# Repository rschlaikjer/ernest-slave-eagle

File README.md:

# Ernest Slave Node Schematics
Eagle files for data collection nodes

[Master Project Repo](https://github.com/rschlaikjer/Ernest)

## What is this
Ernest is the next step of the [ArNest](https://github.com/rschlaikjer/ArNest),
and takes it from a single-location thermostat to a many node system consisting
of a base station and one or more smaller nodes that collect and report
atmospheric data to the base. This way the system can monitor multiple rooms, as
well as the outside conditions.

These EAGLE files show the schematic for hooking up the slave nodes, as well as
a board layout for printing your own slave boards.

For the code to run on the slave nodes,
[see here](https://github.com/rschlaikjer/ernest-slave-code).

## Parts list
(All prices per unit and approximate)

- ($2.00) Atmega 328P (with arduino-style bootloader)
- ($3.19) USB FTDI programmer
- ($1.50) BMP180 breakout board
- ($13.75) (Optional) HIH-6130 humidity sensor
- ($0.98) nrf24L01 wireless transciever
- ($0.39) LM1117 3.3V regulator
- ($0.07) 16 MHz crystal oscillator
- ($0.03) 22pF capacitors
- ($0.08) Momentary reset switch
- ($0.32) 4-pin DIP switch
- ($0.01) 320 Ohm resistors
- ($0.03) LEDs
- ($0.30) 2.5mm barrel jack (for power)

**Total BOM: Approx. $5.86 per board** + 13.75 for humidity, as well as the cost
of PCB manufacture.

## Pretty Pictures

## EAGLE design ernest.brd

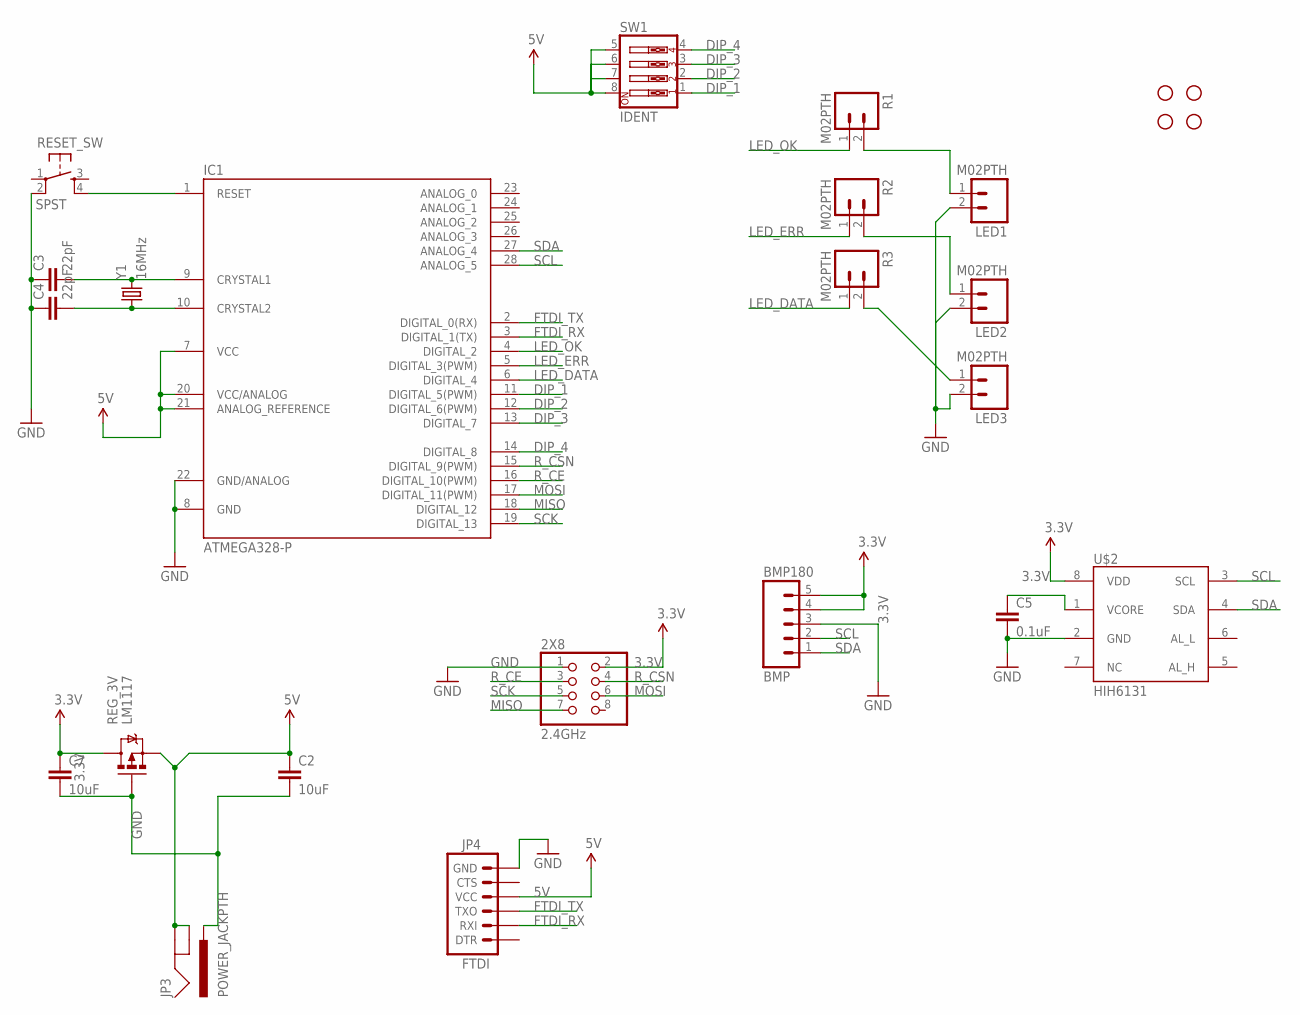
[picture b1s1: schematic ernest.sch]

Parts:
2X8: 2.4GHz; 2X04
BMP180: BMP; 1X05
C2, C7: 10uF; CAP-PTH-SMALL
C3, C4: 22pF; CAP-PTH-SMALL
C5: 0.1uF; CAP-PTH-SMALL
IC1: ATMEGA328-P; DIL28-3
JP3: POWER_JACKPTH; POWER_JACK_PTH
JP4: FTDI; 1X06
LED1, LED2, LED3: M02PTH; 1X02
R1, R2, R3: M02PTH; 1X02
REG_3V: LM1117; TO220V
RESET_SW: SPST; TAC-SWITCH-PTH
STANDOFF1, STANDOFF2, STANDOFF3, STANDOFF4: STAND-OFF
SW1: IDENT; EDG-04
U$2: HIH6131; SOIC8
Y1: 16MHz; HC49US

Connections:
3.3V: 2X8.2, BMP180.4, BMP180.5, C7.1, REG_3V.2 (D), U$2.8 (VDD)
5V: C2.1, IC1.7 (VCC), IC1.20 (VCC/ANALOG), IC1.21 (ANALOG_REFERENCE), JP3.GND, JP3.GNDBREAK, JP4.4 (VCC), REG_3V.3 (S), SW1.5, SW1.6, SW1.7, SW1.8
DIP_1: IC1.11 (DIGITAL_5(PWM)), SW1.1
DIP_2: IC1.12 (DIGITAL_6(PWM)), SW1.2
DIP_3: IC1.13 (DIGITAL_7), SW1.3
DIP_4: IC1.14 (DIGITAL_8), SW1.4
FTDI_RX: IC1.3 (DIGITAL_1(TX)), JP4.2 (RXI)
FTDI_TX: IC1.2 (DIGITAL_0(RX)), JP4.3 (TXO)
GND: 2X8.1, BMP180.3, C2.2, C3.1, C4.1, C5.2, C7.2, IC1.8 (GND), IC1.22 (GND/ANALOG), JP3.PWR, JP4.6 (GND), LED1.2, LED2.2, LED3.2, REG_3V.1 (G), RESET_SW.2, U$2.2 (GND)
LED_DATA: IC1.6 (DIGITAL_4), R3.1
LED_ERR: IC1.5 (DIGITAL_3(PWM)), R2.1
LED_OK: IC1.4 (DIGITAL_2), R1.1
MISO: 2X8.7, IC1.18 (DIGITAL_12)
MOSI: 2X8.6, IC1.17 (DIGITAL_11(PWM))
unnamed: LED1.1, R1.2
unnamed: LED2.1, R2.2
unnamed: LED3.1, R3.2
unnamed: IC1.1 (RESET), RESET_SW.4
unnamed: C5.1, U$2.1 (VCORE)
unnamed: C3.2, IC1.9 (CRYSTAL1), Y1.2
unnamed: C4.2, IC1.10 (CRYSTAL2), Y1.1
R_CE: 2X8.3, IC1.16 (DIGITAL_10(PWM))
R_CSN: 2X8.4, IC1.15 (DIGITAL_9(PWM))
SCK: 2X8.5, IC1.19 (DIGITAL_13)
SCL: BMP180.2, IC1.28 (ANALOG_5), U$2.3 (SCL)
SDA: BMP180.1, IC1.27 (ANALOG_4), U$2.4 (SDA)

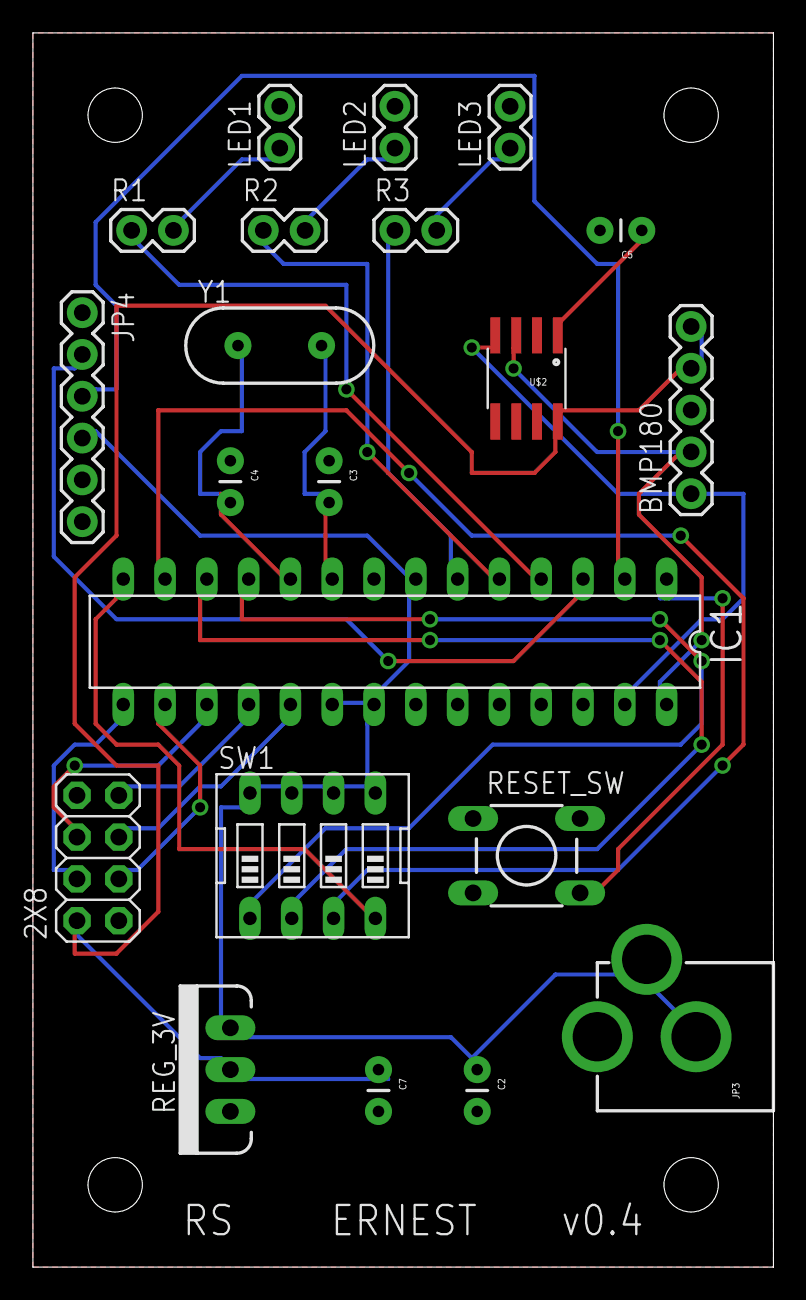
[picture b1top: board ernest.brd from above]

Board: 2 copper layers, 45.0 x 75.0 mm, 25 parts (0 on the bottom side), 26 nets.

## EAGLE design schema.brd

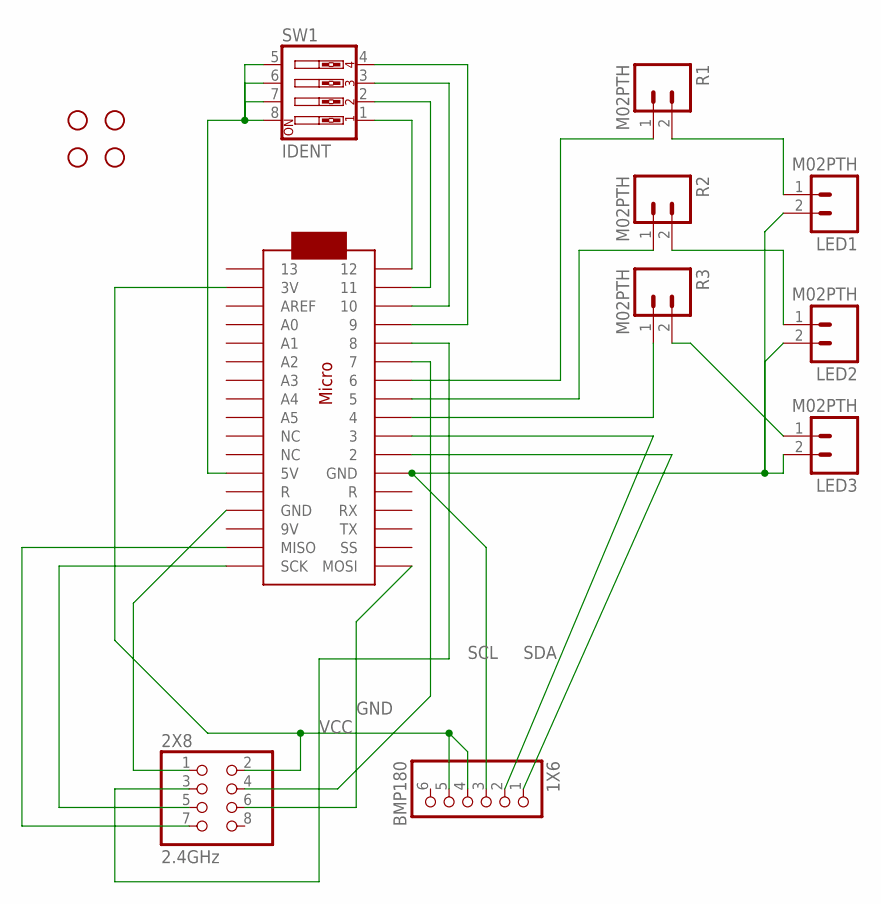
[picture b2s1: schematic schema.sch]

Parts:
1X6: BMP180; 1X06
2X8: 2.4GHz; 2X04
LED1, LED2, LED3: M02PTH; 1X02
R1, R2, R3: M02PTH; 1X02
STANDOFF1, STANDOFF2, STANDOFF3, STANDOFF4: STAND-OFF
SW1: IDENT; EDG-04
U$1: ARDUINOMICRO

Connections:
GND: 1X6.3, 2X8.1, LED1.2, LED2.2, LED3.2, U$1.P$12 (GND), U$1.P$21 (GND)
unnamed: R3.1, U$1.P$9 (4)
unnamed: 2X8.3, U$1.P$5 (8)
unnamed: 2X8.4, U$1.P$6 (7)
unnamed: LED1.1, R1.2
unnamed: LED2.1, R2.2
unnamed: LED3.1, R3.2
unnamed: 2X8.5, U$1.P$18 (SCK)
unnamed: R2.1, U$1.P$8 (5)
unnamed: 2X8.6, U$1.P$17 (MOSI)
unnamed: 2X8.7, U$1.P$19 (MISO)
unnamed: R1.1, U$1.P$7 (6)
unnamed: SW1.5, SW1.6, SW1.7, SW1.8, U$1.P$23 (5V)
unnamed: SW1.1, U$1.P$1 (12)
unnamed: SW1.2, U$1.P$2 (11)
unnamed: SW1.3, U$1.P$3 (10)
unnamed: SW1.4, U$1.P$4 (9)
SCL: 1X6.2, U$1.P$10 (3)
SDA: 1X6.1, U$1.P$11 (2)
VCC: 1X6.4, 1X6.5, 2X8.2, U$1.P$33 (3V)

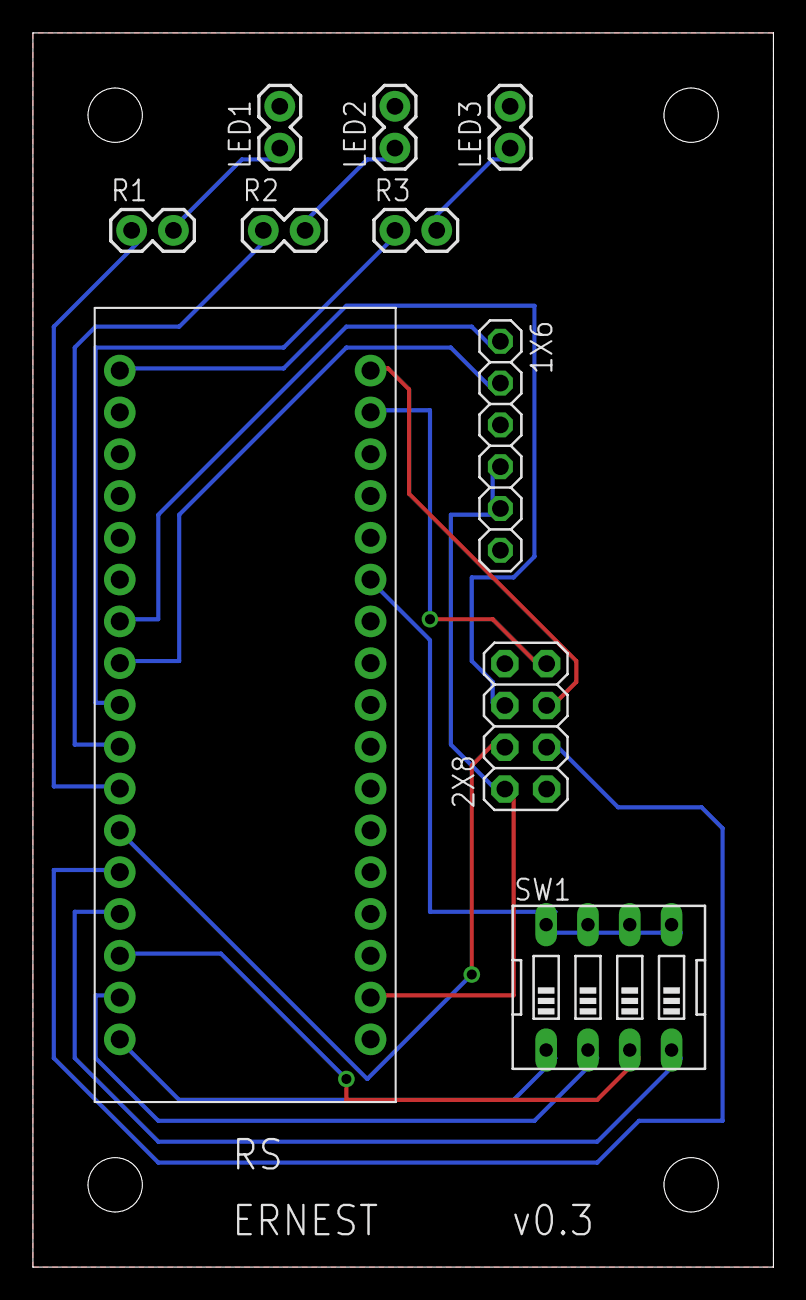
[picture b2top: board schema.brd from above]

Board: 2 copper layers, 45.0 x 75.0 mm, 14 parts (0 on the bottom side), 20 nets.

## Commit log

2015-01-20 ERNEST v0.1
    Mounting for:
    - Arduino Micro
    - BMP180
    - 2.4GHz transciever
    - 3 status LEDs
    - 3 resistors for LEDs
2015-01-20 Add default Eagle gitignore
2015-01-20 ERNEST v0.2
    Added a DIP switch for quick setting of the node ID, to avoid
    having to reflash the thing each time.
2015-01-20 Add README
2015-01-20 Add mounting holes
2015-01-31 Revision 4
    Move away from using an actual Arduino micro to a raw ATMEGA chip to save on
    cost. Also adds in a humidity sensor (Honeywell 6131) to the list of sensors.
2015-01-31 Remove unnecessary 5v reg
2015-02-08 Reorder SPI pins based off breadboard test
2015-02-08 Add rough BOM
2015-02-17 V0.4 release

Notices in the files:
parts and their libraries:
SparkFun-Connectors: Licensing: Creative Commons ShareAlike 4.0 International - https://creativecommons.org/licenses/by-sa/4.0
